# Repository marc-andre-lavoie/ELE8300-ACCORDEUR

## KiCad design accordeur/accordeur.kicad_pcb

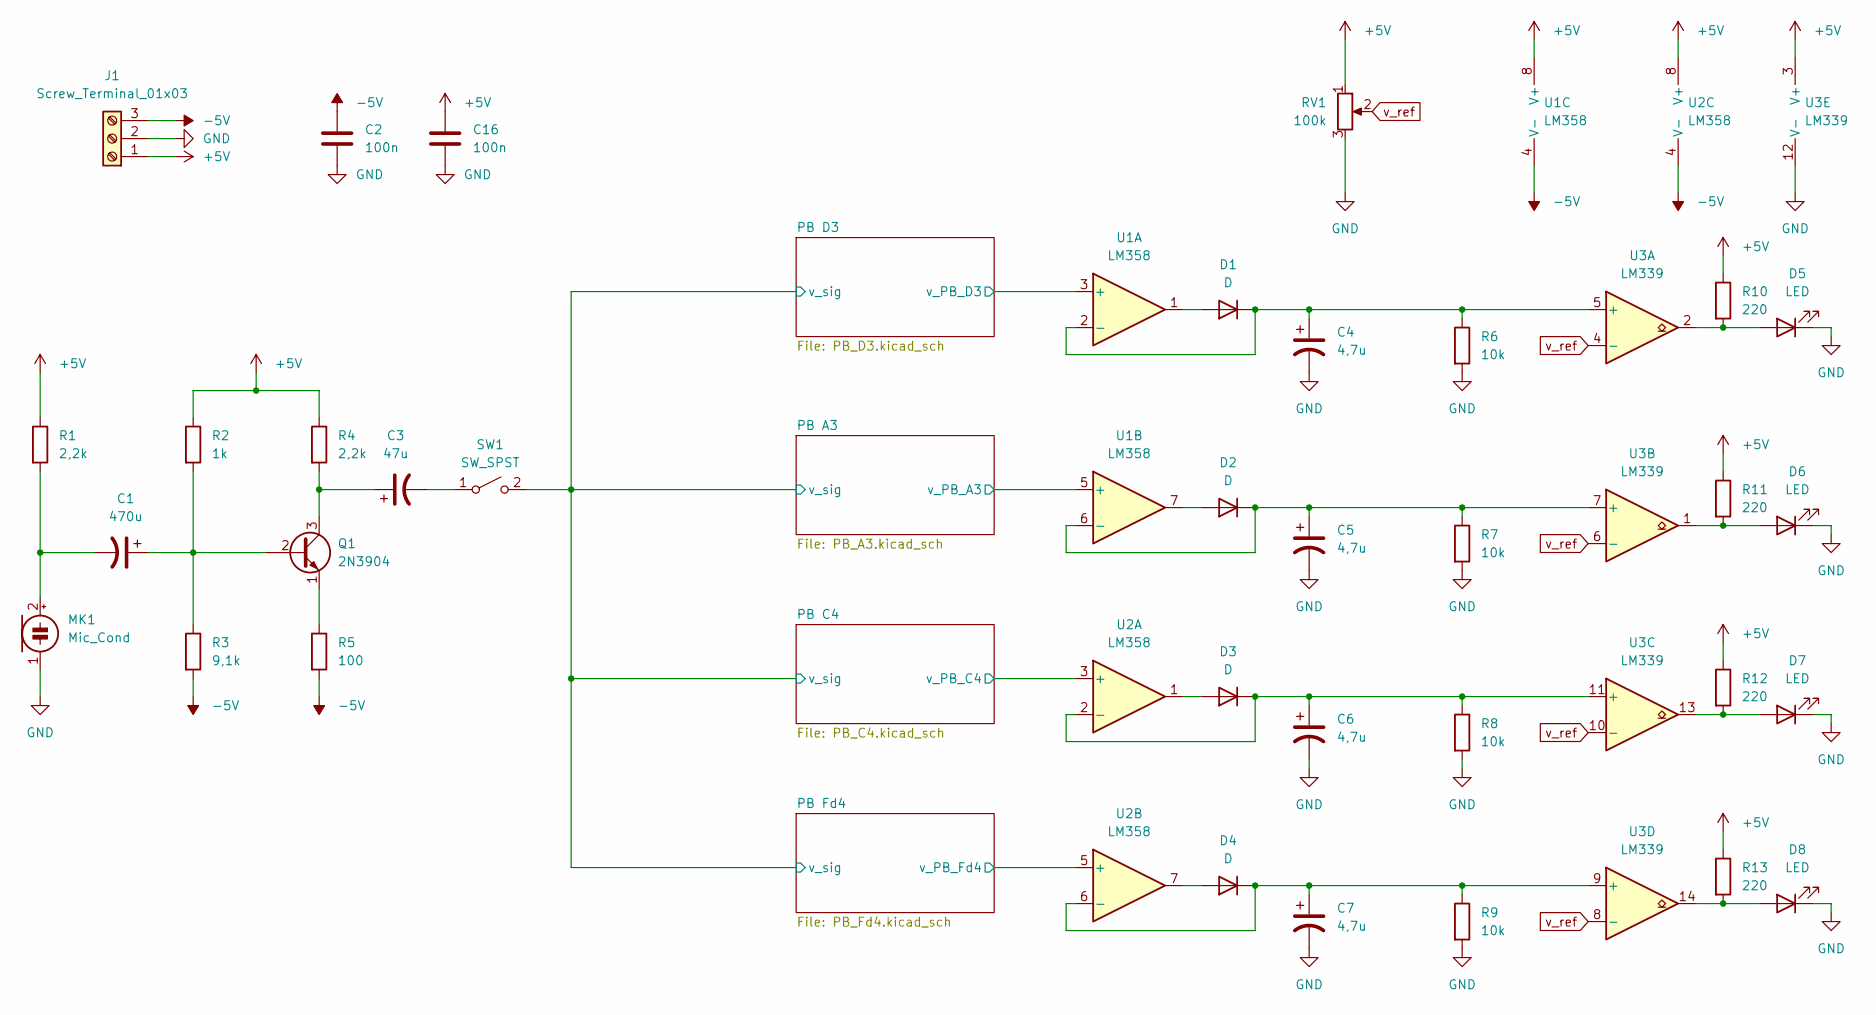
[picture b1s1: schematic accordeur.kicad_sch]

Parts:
C1: 470u; CP_Radial_D7.5mm_P2.50mm
C2, C16: 100n; C_0805_2012Metric_Pad1.18x1.45mm_HandSolder
C3: 47u; CP_Radial_D5.0mm_P2.50mm
C4, C5, C6, C7: 4,7u; CP_Radial_D5.0mm_P2.50mm
D1, D2, D3, D4: D; D_0805_2012Metric_Pad1.15x1.40mm_HandSolder
D5, D6, D7, D8: LED; LED_D5.0mm
J1: Screw_Terminal_01x03; TerminalBlock_bornier-3_P5.08mm
MK1: Mic_Cond; MIC_CMA-4544PF-W
Q1: 2N3904; TO-92_Inline
R1, R4: 2,2k; R_0805_2012Metric_Pad1.20x1.40mm_HandSolder
R2: 1k; R_0805_2012Metric_Pad1.20x1.40mm_HandSolder
R3: 9,1k; R_0805_2012Metric_Pad1.20x1.40mm_HandSolder
R5: 100; R_0805_2012Metric_Pad1.20x1.40mm_HandSolder
R6, R7, R8, R9: 10k; R_0805_2012Metric_Pad1.20x1.40mm_HandSolder
R10, R11, R12, R13: 220; R_0805_2012Metric_Pad1.20x1.40mm_HandSolder
RV1: 100k; POT_emz_marc
SW1: SW_SPST; A11AP
U1, U2: LM358; DIP-8_W7.62mm
U3: LM339; DIP-14_W7.62mm

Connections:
+5V: C16.1, J1.1, R1.1, R2.1, R4.1, R10.1, R11.1, R12.1, R13.1, RV1.1, U1.8 (V+), U2.8 (V+), U3.3 (V+); also elsewhere on the board
-5V: C2.1, J1.3, R3.2, R5.2, U1.4 (V-), U2.4 (V-); also elsewhere on the board
/PB A3/v_PB_A3: U1.5 (+); also elsewhere on the board
/PB A3/v_sig: SW1.2 (B); also elsewhere on the board
/PB C4/v_PB_C4: U2.3 (+); also elsewhere on the board
/PB D3/v_PB_D3: U1.3 (+); also elsewhere on the board
/PB Fd4/v_PB_Fd4: U2.5 (+); also elsewhere on the board
GND: C2.2, C4.2, C5.2, C6.2, C7.2, C16.2, D5.1 (K), D6.1 (K), D7.1 (K), D8.1 (K), J1.2, MK1.1 (-), R6.2, R7.2, R8.2, R9.2, RV1.3, U3.12 (V-); also elsewhere on the board
unnamed: C1.1, Q1.2 (B), R2.2, R3.1
unnamed: C1.2, MK1.2 (+), R1.2
unnamed: C3.1, Q1.3 (C), R4.2
unnamed: C3.2, SW1.1 (A)
unnamed: C4.1, D1.1 (K), R6.1, U1.2 (-), U3.5 (+)
unnamed: C5.1, D2.1 (K), R7.1, U1.6 (-), U3.7 (+)
unnamed: C6.1, D3.1 (K), R8.1, U2.2 (-), U3.11 (+)
unnamed: C7.1, D4.1 (K), R9.1, U2.6 (-), U3.9 (+)
unnamed: D1.2 (A), U1.1
unnamed: D2.2 (A), U1.7
unnamed: D3.2 (A), U2.1
unnamed: D4.2 (A), U2.7
unnamed: D5.2 (A), R10.2, U3.2
unnamed: D6.2 (A), R11.2, U3.1
unnamed: D7.2 (A), R12.2, U3.13
unnamed: D8.2 (A), R13.2, U3.14
unnamed: Q1.1 (E), R5.1
v_ref: RV1.2, U3.4 (-), U3.6 (-), U3.8 (-), U3.10 (-)

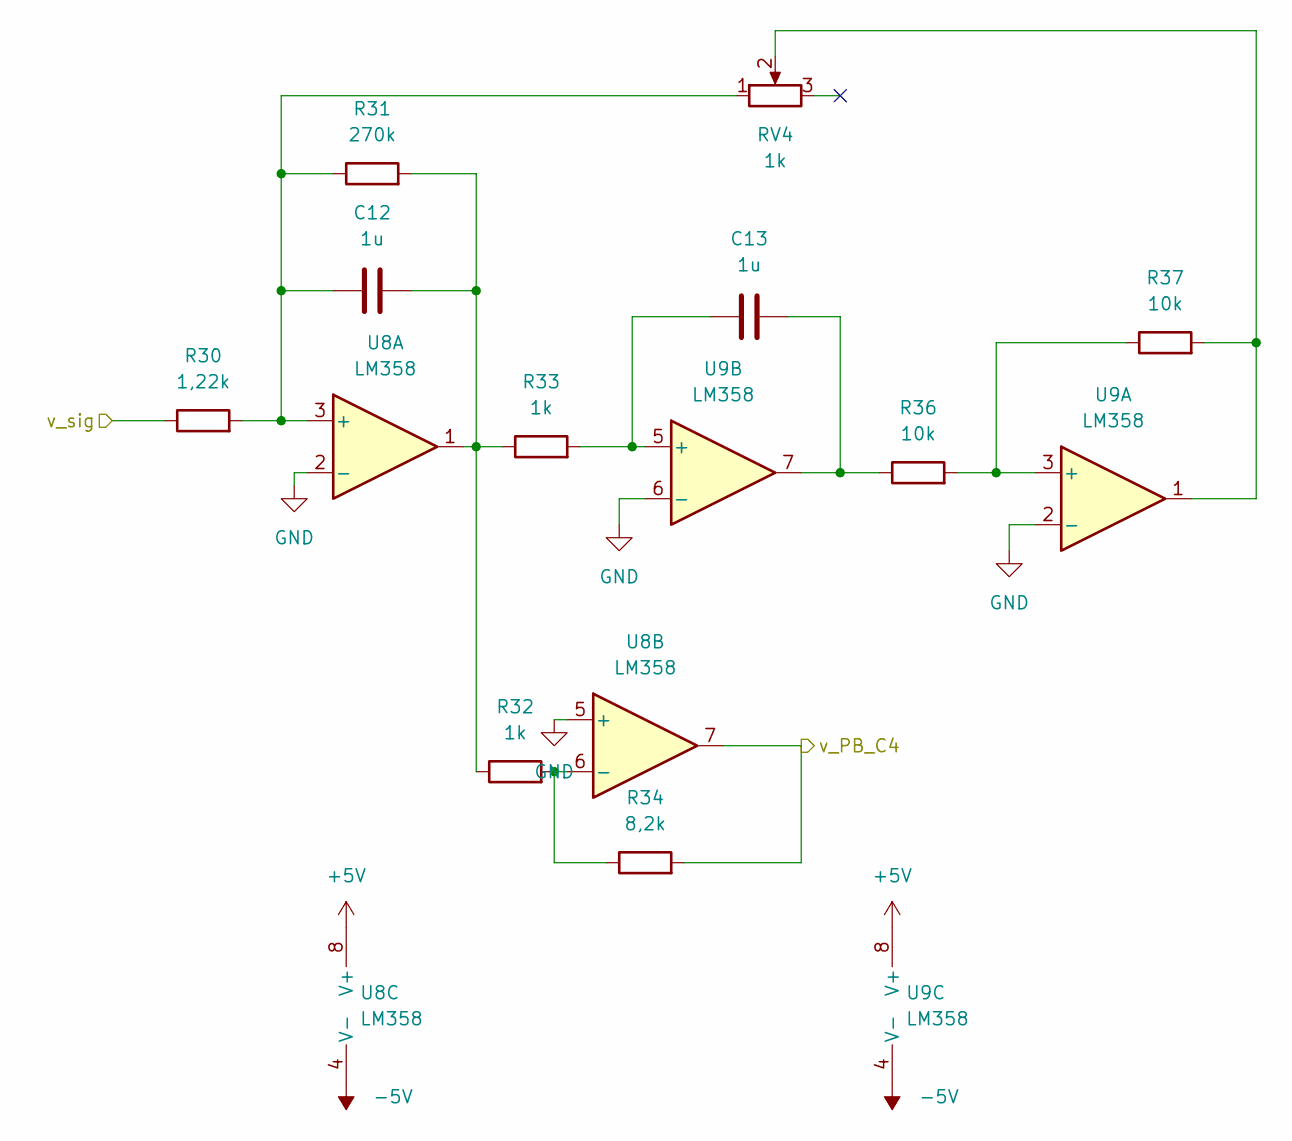
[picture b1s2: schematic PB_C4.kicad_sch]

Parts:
C12, C13: 1u; CP_Radial_D5.0mm_P2.50mm
R30: 1,22k; R_0805_2012Metric_Pad1.20x1.40mm_HandSolder
R31: 270k; R_0805_2012Metric_Pad1.20x1.40mm_HandSolder
R32, R33: 1k; R_0805_2012Metric_Pad1.20x1.40mm_HandSolder
R34: 8,2k; R_0805_2012Metric_Pad1.20x1.40mm_HandSolder
R36, R37: 10k; R_0805_2012Metric_Pad1.20x1.40mm_HandSolder
RV4: 1k; POT_emz_marc
U8, U9: LM358; DIP-8_W7.62mm

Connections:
+5V: U8.8 (V+), U9.8 (V+); also elsewhere on the board
-5V: U8.4 (V-), U9.4 (V-); also elsewhere on the board
/PB A3/v_sig: R30.1; also elsewhere on the board
/PB C4/v_PB_C4: R34.2, U8.7; also elsewhere on the board
GND: U8.2 (-), U8.5 (+), U9.2 (-), U9.6 (-); also elsewhere on the board
unnamed: C12.1, R30.2, R31.1, RV4.1, U8.3 (+)
unnamed: C12.2, R31.2, R32.1, R33.1, U8.1
unnamed: C13.1, R33.2, U9.5 (+)
unnamed: C13.2, R36.1, U9.7
unnamed: R32.2, R34.1, U8.6 (-)
unnamed: R36.2, R37.1, U9.3 (+)
unnamed: R37.2, RV4.2, U9.1

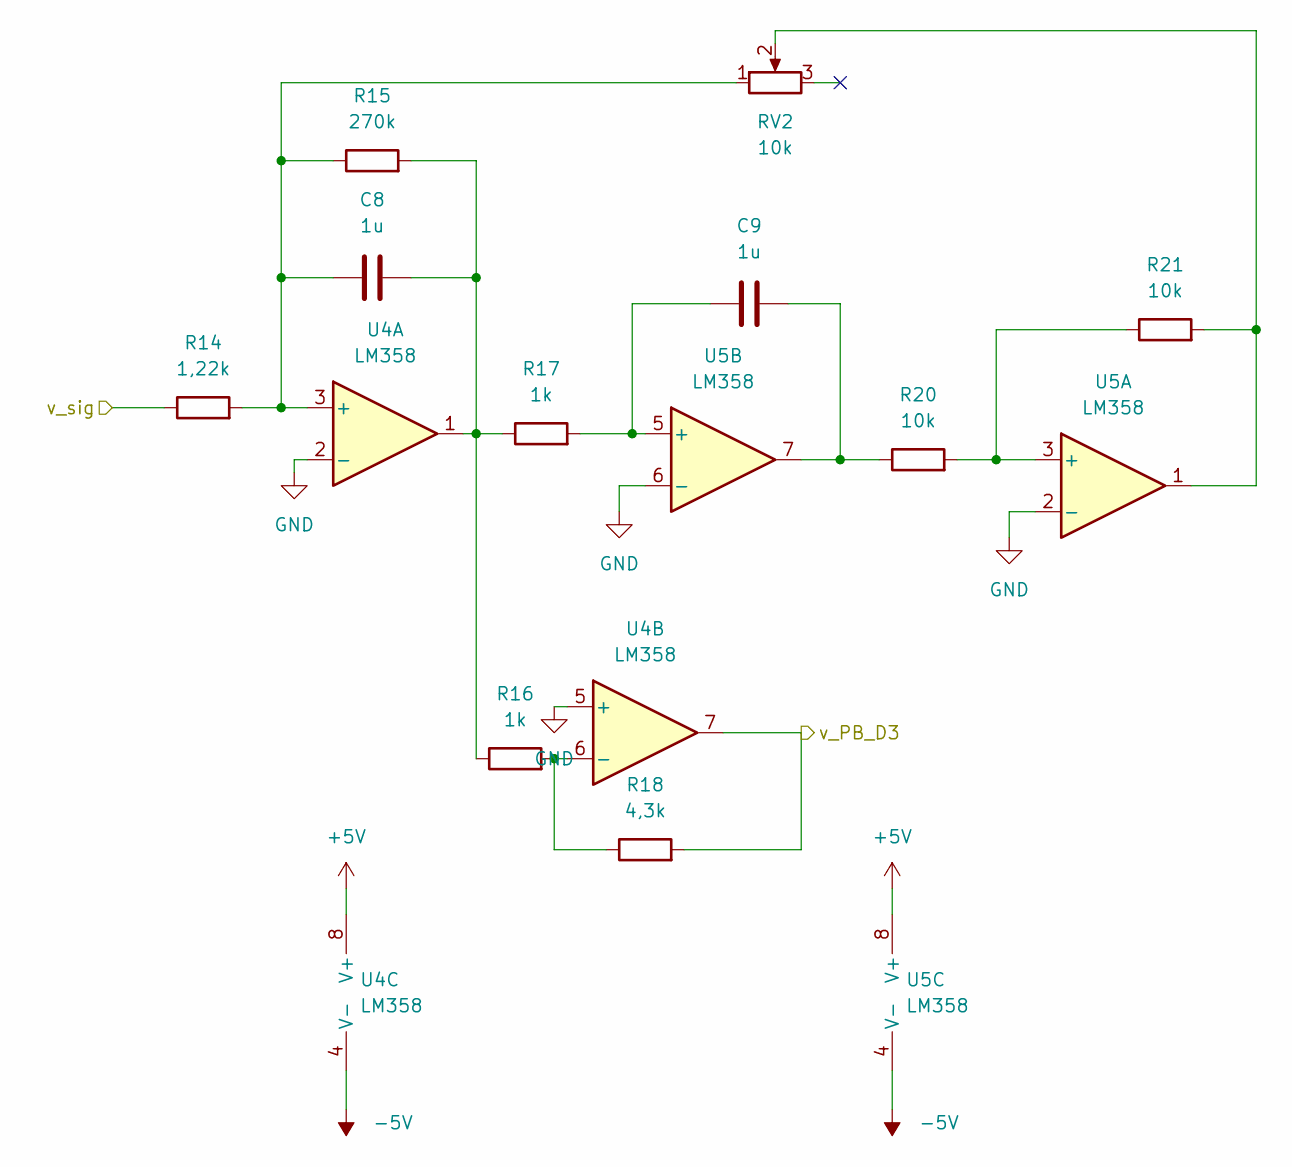
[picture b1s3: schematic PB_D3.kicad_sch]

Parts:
C8, C9: 1u; CP_Radial_D5.0mm_P2.50mm
R14: 1,22k; R_0805_2012Metric_Pad1.20x1.40mm_HandSolder
R15: 270k; R_0805_2012Metric_Pad1.20x1.40mm_HandSolder
R16, R17: 1k; R_0805_2012Metric_Pad1.20x1.40mm_HandSolder
R18: 4,3k; R_0805_2012Metric_Pad1.20x1.40mm_HandSolder
R20, R21: 10k; R_0805_2012Metric_Pad1.20x1.40mm_HandSolder
RV2: 10k; POT_emz_marc
U4, U5: LM358; DIP-8_W7.62mm

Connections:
+5V: U4.8 (V+), U5.8 (V+); also elsewhere on the board
-5V: U4.4 (V-), U5.4 (V-); also elsewhere on the board
/PB A3/v_sig: R14.1; also elsewhere on the board
/PB D3/v_PB_D3: R18.2, U4.7; also elsewhere on the board
GND: U4.2 (-), U4.5 (+), U5.2 (-), U5.6 (-); also elsewhere on the board
unnamed: C8.1, R14.2, R15.1, RV2.1, U4.3 (+)
unnamed: C8.2, R15.2, R16.1, R17.1, U4.1
unnamed: C9.1, R17.2, U5.5 (+)
unnamed: C9.2, R20.1, U5.7
unnamed: R16.2, R18.1, U4.6 (-)
unnamed: R20.2, R21.1, U5.3 (+)
unnamed: R21.2, RV2.2, U5.1

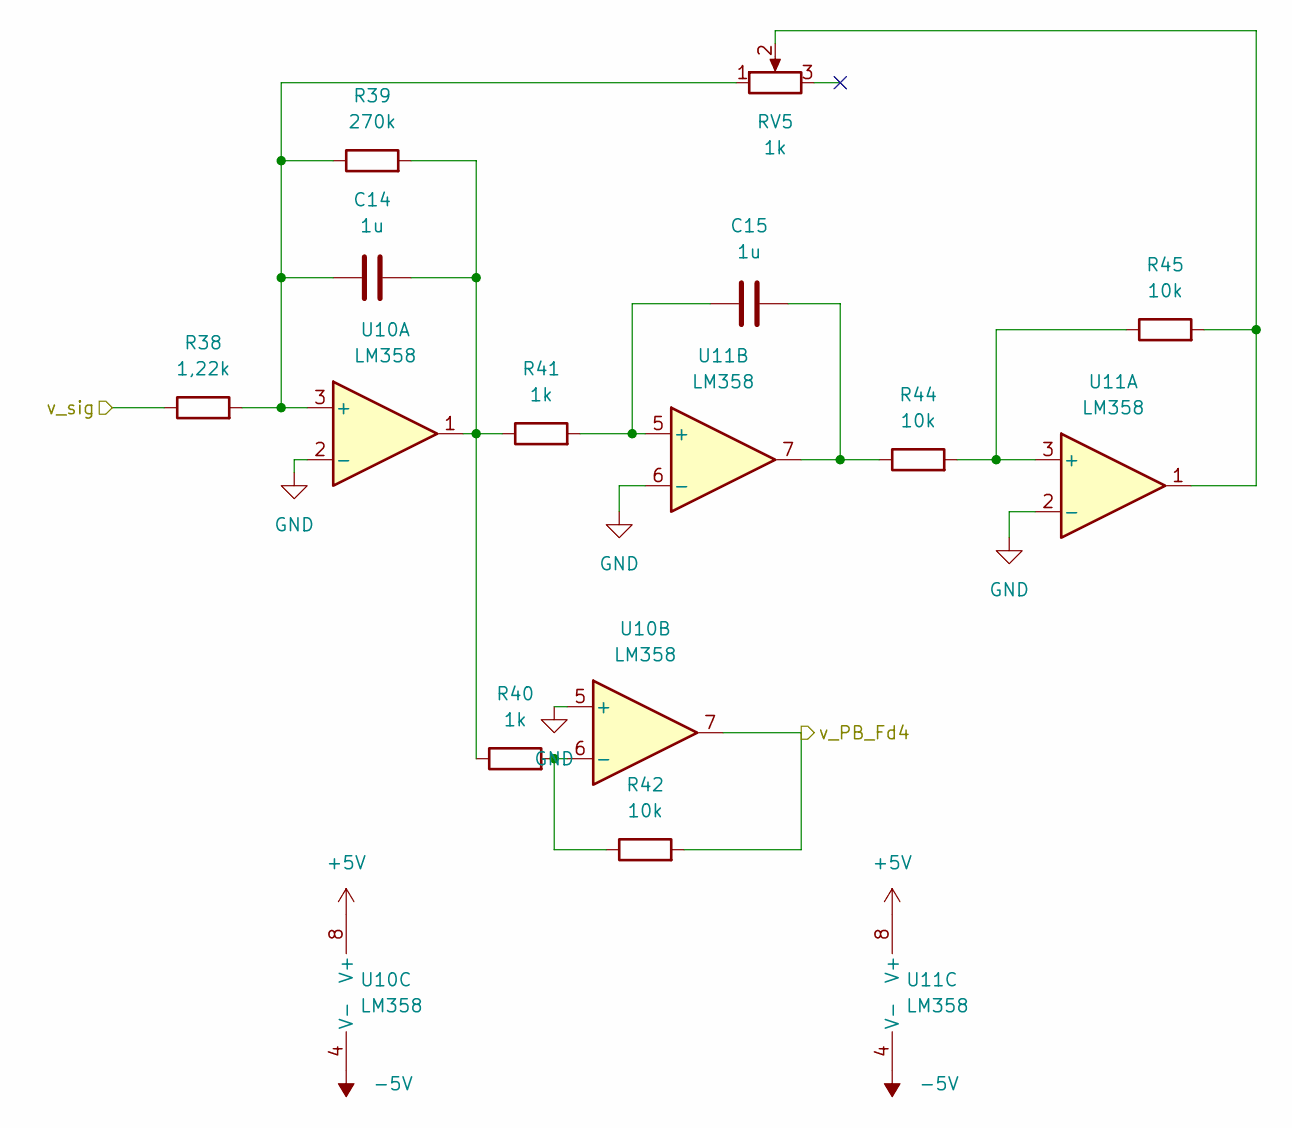
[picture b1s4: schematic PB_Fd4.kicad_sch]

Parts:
C14, C15: 1u; CP_Radial_D5.0mm_P2.50mm
R38: 1,22k; R_0805_2012Metric_Pad1.20x1.40mm_HandSolder
R39: 270k; R_0805_2012Metric_Pad1.20x1.40mm_HandSolder
R40, R41: 1k; R_0805_2012Metric_Pad1.20x1.40mm_HandSolder
R42, R44, R45: 10k; R_0805_2012Metric_Pad1.20x1.40mm_HandSolder
RV5: 1k; POT_emz_marc
U10, U11: LM358; DIP-8_W7.62mm

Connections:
+5V: U10.8 (V+), U11.8 (V+); also elsewhere on the board
-5V: U10.4 (V-), U11.4 (V-); also elsewhere on the board
/PB A3/v_sig: R38.1; also elsewhere on the board
/PB Fd4/v_PB_Fd4: R42.2, U10.7; also elsewhere on the board
GND: U10.2 (-), U10.5 (+), U11.2 (-), U11.6 (-); also elsewhere on the board
unnamed: C14.1, R38.2, R39.1, RV5.1, U10.3 (+)
unnamed: C14.2, R39.2, R40.1, R41.1, U10.1
unnamed: C15.1, R41.2, U11.5 (+)
unnamed: C15.2, R44.1, U11.7
unnamed: R40.2, R42.1, U10.6 (-)
unnamed: R44.2, R45.1, U11.3 (+)
unnamed: R45.2, RV5.2, U11.1

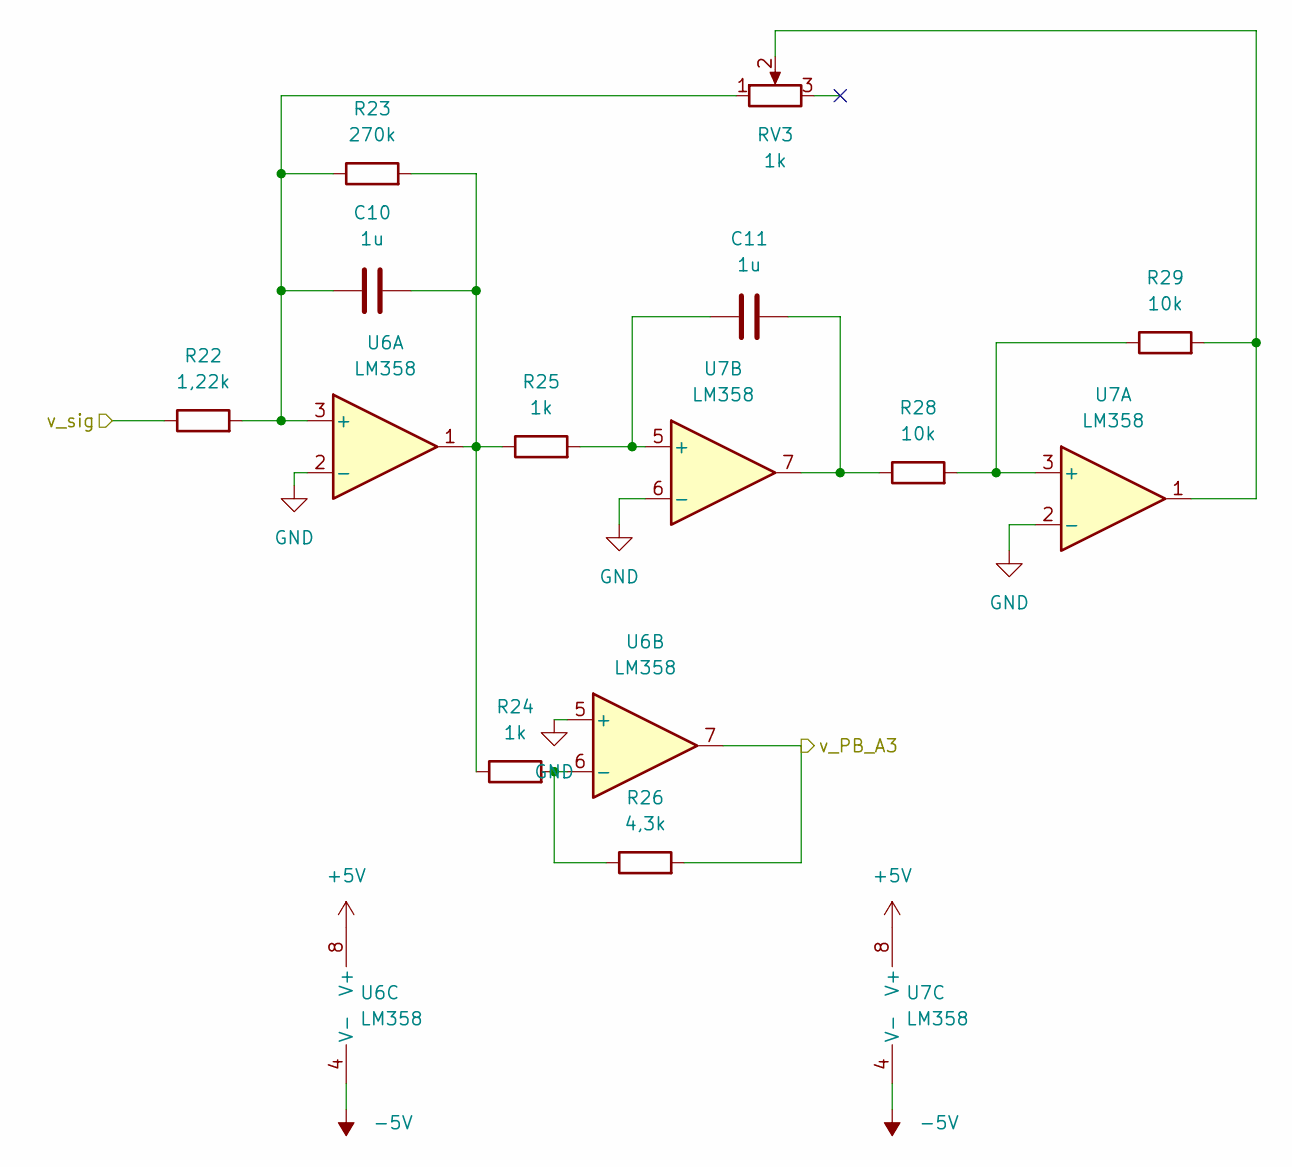
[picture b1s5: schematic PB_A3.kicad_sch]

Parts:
C10, C11: 1u; CP_Radial_D5.0mm_P2.50mm
R22: 1,22k; R_0805_2012Metric_Pad1.20x1.40mm_HandSolder
R23: 270k; R_0805_2012Metric_Pad1.20x1.40mm_HandSolder
R24, R25: 1k; R_0805_2012Metric_Pad1.20x1.40mm_HandSolder
R26: 4,3k; R_0805_2012Metric_Pad1.20x1.40mm_HandSolder
R28, R29: 10k; R_0805_2012Metric_Pad1.20x1.40mm_HandSolder
RV3: 1k; POT_emz_marc
U6, U7: LM358; DIP-8_W7.62mm

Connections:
+5V: U6.8 (V+), U7.8 (V+); also elsewhere on the board
-5V: U6.4 (V-), U7.4 (V-); also elsewhere on the board
/PB A3/v_PB_A3: R26.2, U6.7; also elsewhere on the board
/PB A3/v_sig: R22.1; also elsewhere on the board
GND: U6.2 (-), U6.5 (+), U7.2 (-), U7.6 (-); also elsewhere on the board
unnamed: C10.1, R22.2, R23.1, RV3.1, U6.3 (+)
unnamed: C10.2, R23.2, R24.1, R25.1, U6.1
unnamed: C11.1, R25.2, U7.5 (+)
unnamed: C11.2, R28.1, U7.7
unnamed: R24.2, R26.1, U6.6 (-)
unnamed: R28.2, R29.1, U7.3 (+)
unnamed: R29.2, RV3.2, U7.1

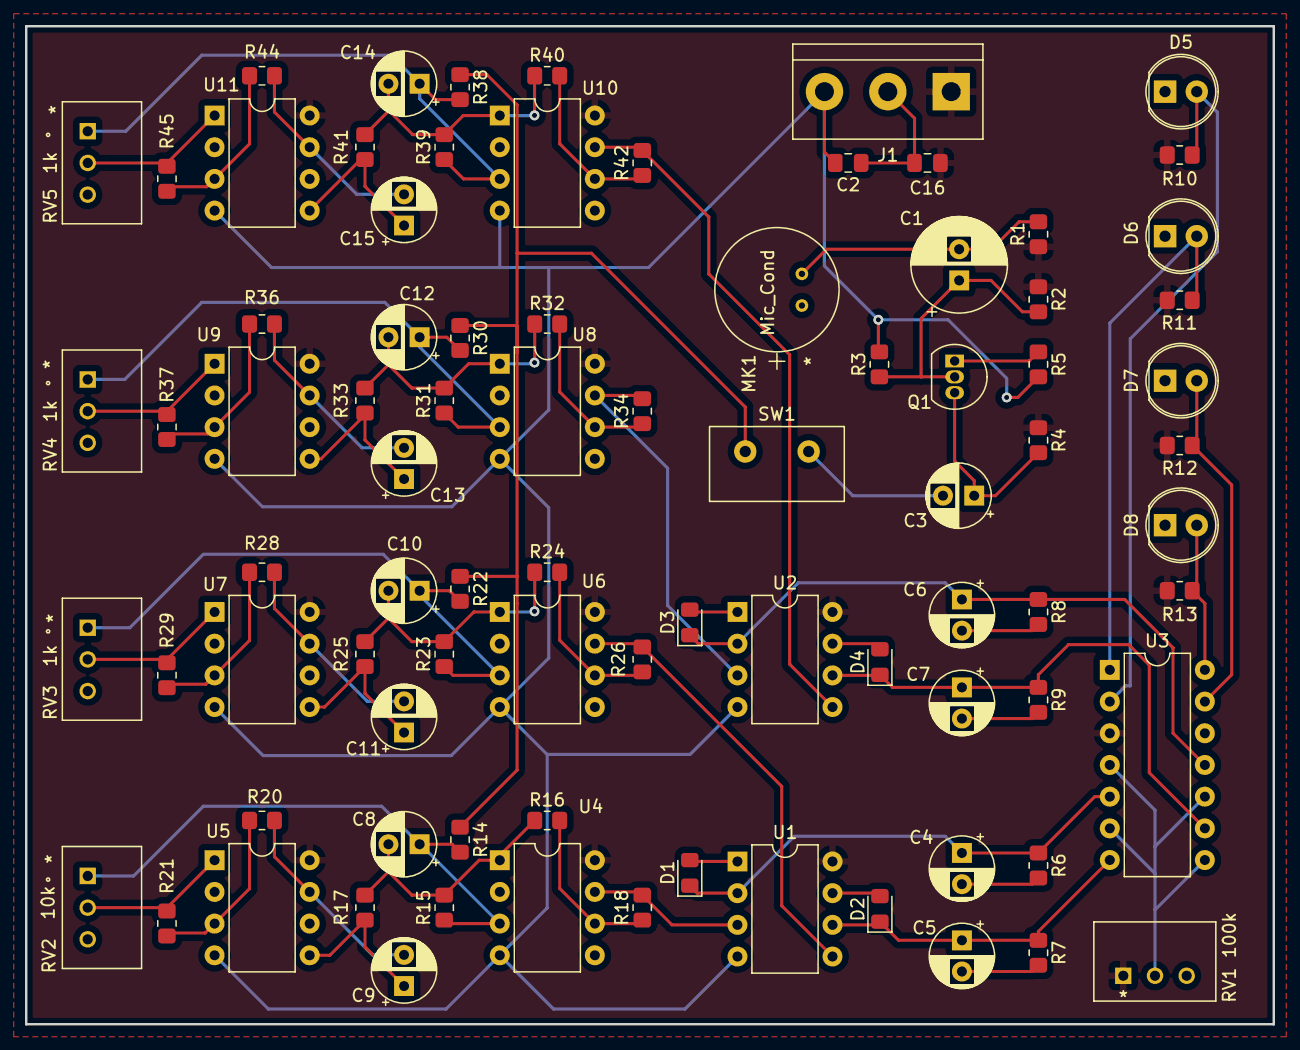
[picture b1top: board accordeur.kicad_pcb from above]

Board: 2 copper layers, 100.0 x 80.0 mm, 85 parts (0 on the bottom side), 54 nets.

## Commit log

2022-03-20 Ajout des fichiers PCB
    Le schematic est bien avancé
2022-03-20 gitignore
    Ajout d'un gitignore
2022-03-20 Changements de Emz
    Ajout de quelques footprints
2022-03-21 Finalisation de la rev 0 du PCB
2022-03-23 Checkpoint dernier review PCB
2022-03-23 Finalisation du placement des pièces
    Prochaine étape : routing
2022-03-24 PCB commandé

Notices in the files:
parts and their libraries:
Copyright 2021 Accelerated Designs. All rights reserved.
